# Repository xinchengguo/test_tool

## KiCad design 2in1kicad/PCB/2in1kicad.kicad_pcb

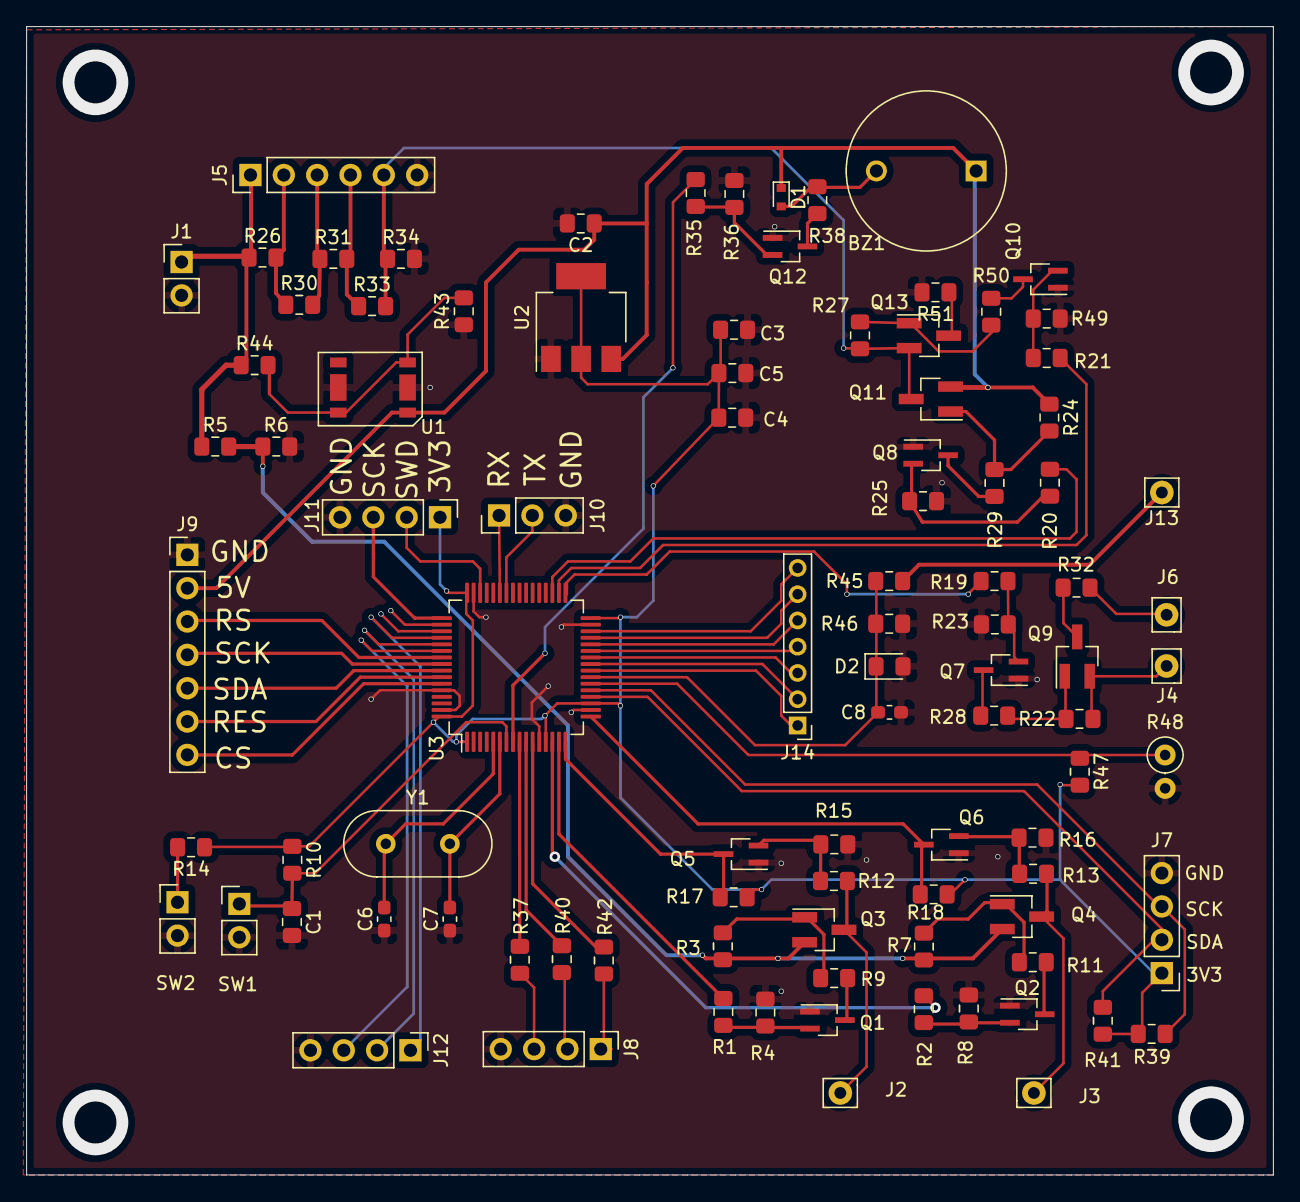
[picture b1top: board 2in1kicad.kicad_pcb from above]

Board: 2 copper layers, 95.0 x 87.5 mm, 95 parts (0 on the bottom side), 78 nets.

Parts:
BZ1: Buzzer; MagneticBuzzer_ProSignal_ABI-010-RC
C1, C2, C3, C4, C5: 0.1uF; C_0805_2012Metric_Pad1.15x1.40mm_HandSolder
C6, C7, C8: 18pF; C_0603_1608Metric_Pad1.05x0.95mm_HandSolder
D1: 1N4148WT; D_SOD-523
D2: 5.1V; D_0805_2012Metric_Pad1.15x1.40mm_HandSolder
J1: DC-20V; PinHeader_1x02_P2.54mm_Vertical
J2: J2_C; Pin_D0.9mm_L10.0mm_W2.4mm_FlatFork
J3: J1_C; Pin_D0.9mm_L10.0mm_W2.4mm_FlatFork
J4: NTC_1; Pin_D0.9mm_L10.0mm_W2.4mm_FlatFork
J5: BAT_R; PinHeader_1x06_P2.54mm_Vertical
J6: NTC_2; Pin_D0.9mm_L10.0mm_W2.4mm_FlatFork
J7: IIC; PinHeader_1x04_P2.54mm_Vertical
J8: LED; PinHeader_1x04_P2.54mm_Vertical
J9: LCD; PinHeader_1x07_P2.54mm_Vertical
J10: UART; PinHeader_1x03_P2.54mm_Vertical
J11: SWIO; PinHeader_1x04_P2.54mm_Vertical
J12: switch; PinHeader_1x04_P2.54mm_Vertical
J13: BATT+; Pin_D0.9mm_L10.0mm_W2.4mm_FlatFork
J14: Conn_01x07_Female; PinHeader_1x07_P2.00mm_Vertical
Q1, Q2, Q5, Q6, Q7, Q8, Q10, Q12: S8050; SOT-323_SC-70_Handsoldering
Q3, Q4, Q9, Q11, Q13: AO3401A; SOT-23_Handsoldering
R1, R2, R4, R5, R6, R8, R9, R10, R11, R12, R13, R14, R15, R16, R17, R18, R19, R20, R21, R23, R25, R26, R28, R29, R30, R31, R32, R33, R34, R35, R36, R38, R39, R41, R45, R46, R47, R49, R50, R51: 10k; R_0805_2012Metric_Pad1.15x1.40mm_HandSolder
R3, R7, R22, R24, R27: 100k; R_0805_2012Metric_Pad1.15x1.40mm_HandSolder
R37, R40, R42: 1k; R_0805_2012Metric_Pad1.15x1.40mm_HandSolder
R43: 1M; R_0805_2012Metric_Pad1.15x1.40mm_HandSolder
R44: 510R; R_0805_2012Metric_Pad1.15x1.40mm_HandSolder
R48: NTC; R_Axial_DIN0207_L6.3mm_D2.5mm_P2.54mm_Vertical
SW1: RST; PinHeader_1x02_P2.54mm_Vertical
SW2: START; PinHeader_1x02_P2.54mm_Vertical
U1: 1142B50; Hsop-6
U2: AP1117-33; SOT-223-3_TabPin2
U3: STM32F103RCTx; LQFP-64_10x10mm_P0.5mm
Y1: Crystal; Crystal_HC49-U_Vertical

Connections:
+3V3: C3.1, C4.1, C5.1, J7.1, J11.1, R10.1, R14.1, R17.1, R18.1, R39.2, R41.2, R47.2, U2.2, U3.1, U3.13, U3.19, U3.32, U3.48, U3.64
+5V: BZ1.1, C2.1, D1.1, J9.2, Q11.2, R24.1, U1.1, U2.3
/+10V: Q3.2, Q4.2, R3.1, R5.2, R6.1, R7.1
/+20V: J1.1, J5.1, R5.1, R26.1, R44.1
/B1: J5.5, Q11.3, Q13.2, R27.1, R33.2, R34.1
/B2: J5.4, R31.2, R33.1
/B3: J5.3, R30.2, R31.1
/B4: J5.2, R26.2, R30.1
/BAT_ADC: C8.2, D2.1, R45.1, R46.2, U3.23
/Buzzer: R35.1, U3.8
/Con1: J14.1, U3.24
/Con2: J14.2, U3.25
/Con3: J14.3, U3.26
/Con4: J14.4, U3.27
/Con5: J14.5, U3.28
/Con6: J14.6, U3.29
/Con7: J14.7, U3.30
/J1: J3.1, Q4.3, R13.1
/J1_EN: R2.1, U3.14
/J1_T: Q6.3, R18.2, U3.17
/J2: J2.1, Q3.3, R12.1
/J2_EN: R1.1, U3.15
/J2_T: Q5.3, R17.2, U3.16
/LCD_CS: J9.7, U3.59
/LCD_D6: J9.4, U3.56
/LCD_D7: J9.5, U3.57
/LCD_RES: J9.6, U3.58
/LCD_RS: J9.3, U3.55
/LED1: R37.2, U3.9
/LED2: R40.2, U3.10
/LED3: R42.2, U3.11
/NRST: C1.1, R10.2, SW1.1, U3.7
/NTC_ADC: R47.1, R48.1, U3.22
/OTA_EN: R19.1, U3.33
/OVA_EN: R20.1, U3.35
/SCK: J7.3, R39.1, U3.21
/SCLK: J11.3, U3.49
/SDA: J7.2, R41.1, U3.20
/ST1: J12.1, U3.52
/ST2: J12.2, U3.53
/ST3: J12.3, U3.54
/START: R14.2, SW2.1
/SWD: J11.2, U3.46
/UVA_EN: R21.1, U3.34
GND: C1.2, C2.2, C3.2, C4.2, C5.2, C6.1, C7.1, C8.1, D2.2, J1.2, J5.6, J7.4, J8.4, J9.1, J10.3, J11.4, J12.4, Q1.1, Q2.1, Q5.1, Q6.1, Q7.1, Q8.1, Q10.1, Q12.1, R4.2, R6.2, R8.2, R15.2, R16.2, R23.2, R25.2, R34.2, R36.2, R43.1, R46.1, R48.2, R49.2, R51.2, SW1.2, SW2.2, U1.2, U1.5, U2.1, U3.12, U3.18, U3.31, U3.47, U3.60, U3.63
unnamed: BZ1.2, D1.2, R38.2
unnamed: C6.2, U3.5, Y1.1
unnamed: C7.2, U3.6, Y1.2
unnamed: J4.1, Q9.2, R22.1
unnamed: J6.1, R32.2
unnamed: J8.1, R42.1
unnamed: J8.2, R40.1
unnamed: J8.3, R37.1
unnamed: J10.1, U3.43
unnamed: J10.2, U3.42
unnamed: J13.1, R45.2
unnamed: Q1.2, R1.2, R4.1
unnamed: Q1.3, R9.2
unnamed: Q2.2, R2.2, R8.1
unnamed: Q2.3, R11.2
unnamed: Q3.1, R3.2, R9.1
unnamed: Q4.1, R7.2, R11.1
unnamed: Q5.2, R12.2, R15.1
unnamed: Q6.2, R13.2, R16.1
unnamed: Q7.2, R19.2, R23.1
unnamed: Q7.3, R28.2
unnamed: Q8.2, R20.2, R25.1
unnamed: Q8.3, R29.2
unnamed: Q9.1, R22.2, R28.1
unnamed: Q9.3, R32.1
unnamed: Q10.2, R21.2, R49.1
unnamed: Q10.3, R50.2
unnamed: Q11.1, R24.2, R29.1
unnamed: Q12.2, R35.2, R36.1
unnamed: Q12.3, R38.1
unnamed: Q13.1, R27.2, R50.1
unnamed: Q13.3, R51.1
unnamed: R43.2, R44.2, U1.3, U1.6

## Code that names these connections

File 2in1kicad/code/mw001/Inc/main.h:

/* USER CODE BEGIN Header */
/**
  ******************************************************************************
  * @file           : main.h
  * @brief          : Header for main.c file.
  *                   This file contains the common defines of the application.
  ******************************************************************************
  * @attention
  *
  * <h2><center>&copy; Copyright (c) 2020 STMicroelectronics.
  * All rights reserved.</center></h2>
  *
  * This software component is licensed by ST under BSD 3-Clause license,
  * the "License"; You may not use this file except in compliance with the
  * License. You may obtain a copy of the License at:
  *                        opensource.org/licenses/BSD-3-Clause
  *
  ******************************************************************************
  */
/* USER CODE END Header */

/* Define to prevent recursive inclusion -------------------------------------*/
#ifndef __MAIN_H
#define __MAIN_H

#ifdef __cplusplus
extern "C" {
#endif

/* Includes ------------------------------------------------------------------*/
#include "stm32f1xx_hal.h"

/* Private includes ----------------------------------------------------------*/
/* USER CODE BEGIN Includes */

/* USER CODE END Includes */

/* Exported types ------------------------------------------------------------*/
/* USER CODE BEGIN ET */

/* USER CODE END ET */

/* Exported constants --------------------------------------------------------*/
/* USER CODE BEGIN EC */

/* USER CODE END EC */

/* Exported macro ------------------------------------------------------------*/
/* USER CODE BEGIN EM */

/* USER CODE END EM */

/* Exported functions prototypes ---------------------------------------------*/
void Error_Handler(void);

/* USER CODE BEGIN EFP */

/* USER CODE END EFP */

/* Private defines -----------------------------------------------------------*/
#define BUZZ_Pin GPIO_PIN_0
#define BUZZ_GPIO_Port GPIOC
#define LED1_Pin GPIO_PIN_1
#define LED1_GPIO_Port GPIOC
#define LED2_Pin GPIO_PIN_2
#define LED2_GPIO_Port GPIOC
#define LED3_Pin GPIO_PIN_3
#define LED3_GPIO_Port GPIOC
#define J1_EN_Pin GPIO_PIN_0
#define J1_EN_GPIO_Port GPIOA
#define J2_EN_Pin GPIO_PIN_1
#define J2_EN_GPIO_Port GPIOA
#define J2_T_Pin GPIO_PIN_2
#define J2_T_GPIO_Port GPIOA
#define J1_T_Pin GPIO_PIN_3
#define J1_T_GPIO_Port GPIOA
#define IIC_SDA_Pin GPIO_PIN_4
#define IIC_SDA_GPIO_Port GPIOA
#define IIC_SCK_Pin GPIO_PIN_5
#define IIC_SCK_GPIO_Port GPIOA
#define NTC_ADC_Pin GPIO_PIN_6
#define NTC_ADC_GPIO_Port GPIOA
#define BAT_ADC_Pin GPIO_PIN_7
#define BAT_ADC_GPIO_Port GPIOA
#define OTA_EN_Pin GPIO_PIN_12
#define OTA_EN_GPIO_Port GPIOB
#define UVA_EN_Pin GPIO_PIN_13
#define UVA_EN_GPIO_Port GPIOB
#define OVA_EN_Pin GPIO_PIN_14
#define OVA_EN_GPIO_Port GPIOB
#define ST1_Pin GPIO_PIN_11
#define ST1_GPIO_Port GPIOC
#define ST2_Pin GPIO_PIN_12
#define ST2_GPIO_Port GPIOC
#define ST3_Pin GPIO_PIN_2
#define ST3_GPIO_Port GPIOD
#define LCD_RS_Pin GPIO_PIN_3
#define LCD_RS_GPIO_Port GPIOB
#define LCD_SCK_Pin GPIO_PIN_4
#define LCD_SCK_GPIO_Port GPIOB
#define LCD_SDA_Pin GPIO_PIN_5
#define LCD_SDA_GPIO_Port GPIOB
#define LCD_RES_Pin GPIO_PIN_6
#define LCD_RES_GPIO_Port GPIOB
#define LCD_CS_Pin GPIO_PIN_7
#define LCD_CS_GPIO_Port GPIOB
/* USER CODE BEGIN Private defines */

/* USER CODE END Private defines */

#ifdef __cplusplus
}
#endif

#endif /* __MAIN_H */

/************************ (C) COPYRIGHT STMicroelectronics *****END OF FILE****/

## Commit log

2020-07-28 提交图纸
2020-07-28 第一次提交
